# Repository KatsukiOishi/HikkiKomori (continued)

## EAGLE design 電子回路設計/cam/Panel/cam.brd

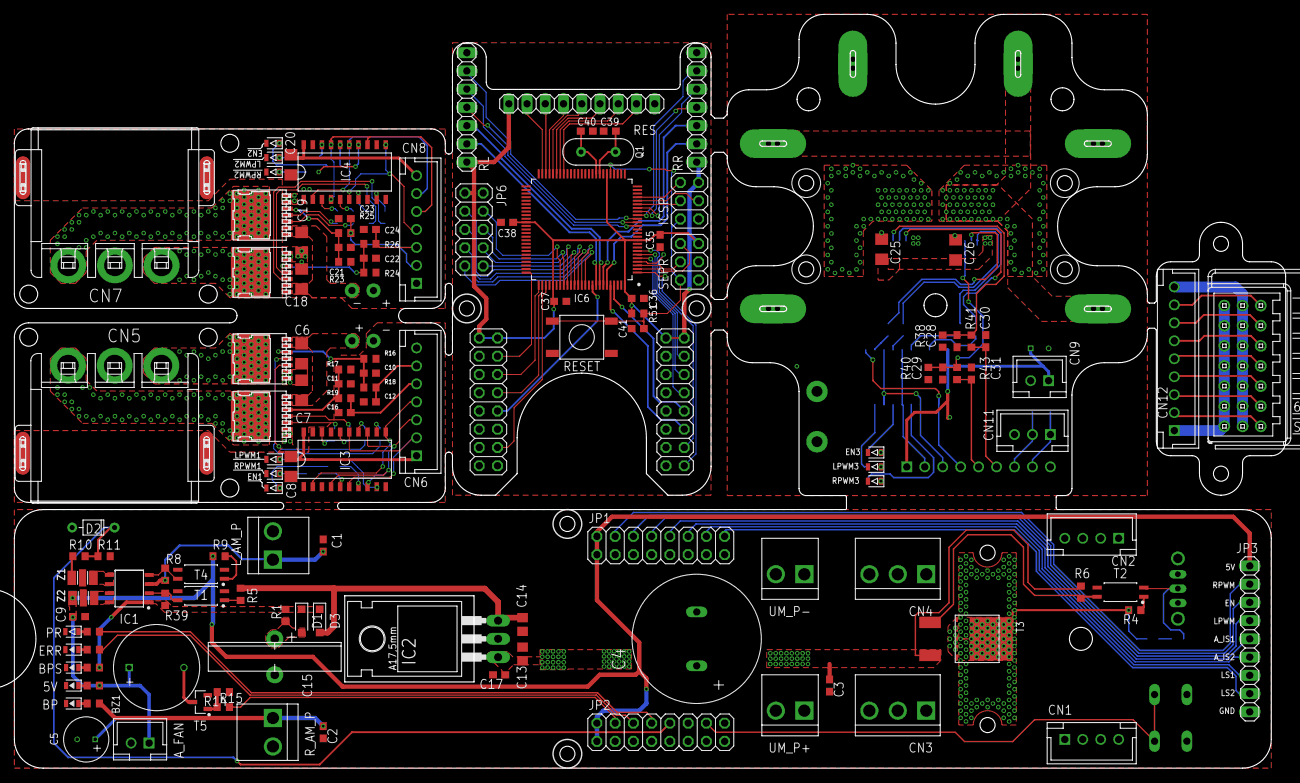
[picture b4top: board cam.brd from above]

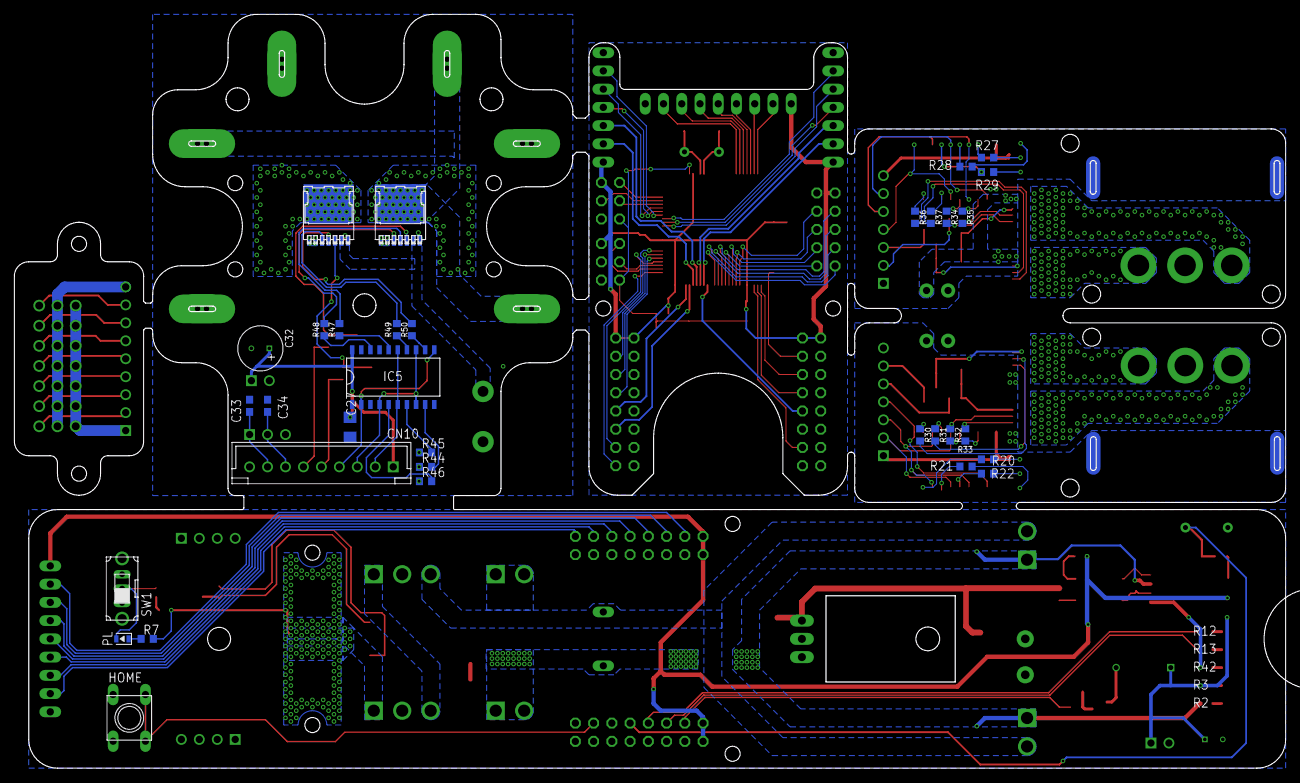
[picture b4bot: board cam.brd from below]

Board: 2 copper layers, 177.0 x 105.0 mm, 175 parts (33 on the bottom side), 171 nets.

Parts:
5V: OSBL1608C1A; LEDC1608X39N_B
A_FAN: B2B-XH-A
BP: OSBL1608C1A; LEDC1608X39N_B
BPS: OSBL1608C1A; LEDC1608X39N_B
BZ1: UGCM1205XP
C1, C2, C3, C9, C17, C35, C36, C37, C38: 0.1u; C0603
C4: 3300u; D18_L25_P7.5_D1
C5, C32: 100u; CPOL6.3-7_2.5
C6, C7, C8, C18, C19, C20, C25, C26, C27: 10u; C3216
C10, C11, C21, C22, C28, C29, C33, C34: 1n; C1608
C12, C16, C23, C24, C30, C31: 0.1u; C1608
C13, C14: 10u; C0805
C15: SE-5R5-D105VYV
C39, C40, C41: 22p; C0603
CN1, CN2: B4B-XH-A
CN3, CN4: B3P-VH
CN5, CN7: 798-HVH-280-3P-6.5DS
CN6, CN8: B7B-XH-A
CN9: B2B-XH-A
CN10, CN12: B9B-XH-A
CN11: B3B-XH-A
D1, D3: SS2040FL; SOD-123
D2: GDZJ5.1ADO-34; DIOAD590W50L290D210B
EN1, EN2, EN3: OSTG1608C1A; LEDC1608X39N_G
ERR: OSHR1608C1A; LEDC1608X39N_R
HOME: TS-0606-F-N-BLK; TS-0606-F-N
IC1: FDS4935A; SOIC127P600X250-8N
IC2: NJM7805FA-I; TO220
IC3, IC4, IC5: TC74HC244AF; SOP20
IC6: ATMEGA2560-16AU; QFP100
ICSP: 2X03
JP1, JP2, JP4, JP5: 2X08
JP3: 1X09
JP6: 2X05
LPWM1, LPWM2, LPWM3: OSTG1608C1A; LEDC1608X39N_G
L_AM_P: B2P-VH
OUT1: VIA_2.5X5.25_D0.75; VIA_2X5.25_D0.75
PL: OSBL1608C1A; LEDC1608X39N_B
PR: OSTG1608C1A; LEDC1608X39N_G
Q1: HUSG-16.000-20; XTALRR480W50L990T368H350B
R1, R15: 10; R0603
R2, R3, R7, R11, R12, R13, R14, R20, R21, R22, R27, R28, R29, R42, R44, R45, R46: 1k; R0603
R4: 480; R0603
R5, R9: 100; R0603
R6, R8, R39, R51: 10k; R0603
R10: 4.7k; R0603
R16, R17, R23, R24, R38, R40: 1.5k; R0603
R18, R19, R25, R26, R41, R43: 150; R0603
R30, R31, R32, R33, R34, R35, R36, R37, R47, R48, R49, R50: 10k; R1608
RES: 1X09
RESET: TS-06104
RL: 1X07
RPWM1, RPWM2, RPWM3: OSTG1608C1A; LEDC1608X39N_G
RR: 1X07
R_AM_P: B2P-VH
SEPR: 2X03
SW1: SS-12D01-VG4
T1, T2, T4: TLP291; SOIC127P700X210-4N
T3: TJ60S04M3L; DPACK
T5: IRLML6344TRPBF; SOT95P240X110-3N
U1, U2, U3, U4, U5, U6: BTN9990LV
U$1: R3006B
U$2, U$4, U$5, U$6, U$7, U$8, U$9, U$10, U$11, U$12, U$13: VIA_2.5X5.25_D0.75; VIA_2X5.25_D0.75
UM_P+: B2P-VH
UM_P-: B2P-VH
Z1, Z2: NFE31PT; NFE31

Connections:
5V: CN12.9, U$1.V1, U$1.V2, U$1.V3, U$1.V4, U$1.V5, U$1.V6, U$1.VB
5V1: IC1.7, IC1.8, Z2.1
+5V: A_FAN.1, BZ1.+, C5.+, C9.1, JP1.1, JP1.2, JP2.1, JP2.2, JP3.1, R3.2, R9.2, Z2.3
+5V1: C35.1, C36.1, C37.1, C38.1, IC6.10, IC6.31, IC6.61, IC6.80, IC6.100, ICSP.2, JP4.1, JP4.2, JP5.1, JP5.2, JP6.1, R51.2, RES.1, RL.1, RR.1, SEPR.2
+18V: CN3.1, R4.2, R7.2, T3.2
A_DIR: IC6.5, JP4.8
A_EN: IC6.6, JP4.6
A_IS1: JP1.10, JP3.5
A_IS2: JP1.12, JP3.6
A_IS3: IC6.97, JP4.10
A_IS4: IC6.96, JP4.12
A_PWM: IC6.7, JP4.4
BLINE2: CN3.3, CN4.1
BPS_LINE: D1.1, D3.1, IC1.1, R1.2, R39.2, R42.2
BPS_OR: C15.+, D1.2, R1.1
BUZ: JP2.4, R15.2
BUZ1: IC6.75, JP5.4
EN: JP1.6, JP3.3
EN1: CN6.3, IC3.4, IC3.8, IC3.13
EN2: CN8.5, IC4.4, IC4.13, IC4.17
EN3: CN10.3, IC5.4, IC5.8, IC5.13
ERR_LED: JP2.6, R13.2
ERR_LED1: IC6.76, JP5.6
GND: 5V.2, A_FAN.2, BP.2, BPS.2, C1.2, C2.2, C3.2, C4.-, C5.-, C9.2, C13.2, C14.2, C15.-, C17.2, CN4.3, D2.2, ERR.2, HOME.T3, HOME.T4, IC2.2, JP1.3, JP1.5, JP1.7, JP1.9, JP1.11, JP1.13, JP1.15, JP2.3, JP2.5, JP2.7, JP2.9, JP2.11, JP2.12, JP2.13, JP2.15, JP2.16, JP3.9, L_AM_P.2, PR.K, R11.1, R14.1, R_AM_P.2, SW1.NO, T1.2, T1.3, T2.3, T4.2, T4.3, T5.2, UM_P-.1, UM_P-.2, Z1.2, Z2.2
GND1: C6.2, C7.2, C8.2, C10.2, C11.2, C12.2, C16.2, C18.2, C19.2, C20.2, C21.2, C22.2, C23.2, C24.2, CN5.P$1, CN5.P$2, CN5.P$3, CN5.P$4, CN6.7, CN7.P$1, CN7.P$2, CN7.P$3, CN7.P$4, CN8.1, EN1.K, EN2.K, IC3.1, IC3.10, IC3.19, IC4.1, IC4.10, IC4.19, LPWM1.K, LPWM2.K, R16.1, R17.1, R23.1, R24.1, RPWM1.K, RPWM2.K, U1.GND1, U1.GND2, U2.GND1, U2.GND2, U3.GND1, U3.GND2, U4.GND1, U4.GND2
GND2: C25.2, C26.2, C27.2, C28.2, C29.2, C30.2, C31.2, C32.-, C33.2, C34.2, CN9.2, CN10.9, CN11.3, EN3.K, IC5.1, IC5.10, IC5.19, LPWM3.K, R38.1, R40.1, RPWM3.K, U5.GND1, U5.GND2, U6.GND1, U6.GND2
GND3: C35.2, C36.2, C37.2, C38.2, C39.1, C40.1, C41.2, IC6.11, IC6.32, IC6.62, IC6.81, IC6.99, ICSP.6, JP4.3, JP4.5, JP4.7, JP4.9, JP4.11, JP4.13, JP4.15, JP5.3, JP5.5, JP5.7, JP5.9, JP5.11, JP5.12, JP5.13, JP5.15, JP5.16, JP6.2, RES.9, RESET.B1, RESET.B2, RL.7, RR.7, SEPR.6
GND4: CN12.1, U$1.0B, U$1.01, U$1.02, U$1.03, U$1.04, U$1.05, U$1.06
HOME_SW: HOME.T1, HOME.T2, JP2.14
HOME_SW1: IC6.78, JP5.14
IS1: C12.1, CN6.6, R18.1
IS1_A: C10.1, R16.2, R18.2, U1.IS
IS1_A1: C21.1, R23.2, R25.2, U3.IS
IS1_A2: C28.1, R38.2, R41.2, U5.IS
IS2: C16.1, CN6.5, R19.1
IS2_1: C11.1, R17.2, R19.2, U2.IS
IS2_2: C22.1, R24.2, R26.2, U4.IS
IS2_3: C29.1, R40.2, R43.2, U6.IS
IS3: C30.1, CN10.6, R41.1
IS4: C31.1, CN10.5, R43.1
IS12: C23.1, CN8.2, R25.1
IS22: C24.1, CN8.3, R26.1
LPWM: JP1.8, JP3.4
LPWM1: CN6.4, IC3.2, IC3.11
LPWM2: CN8.4, IC4.6, IC4.11
LPWM3: CN10.4, IC5.2, IC5.11
LS1: JP1.14, JP3.7
LS2: JP1.16, JP3.8
LS3: C33.1, CN10.8, CN11.1
LS4: C34.1, CN10.7, CN11.2
LS5: IC6.4, JP4.14
LS6: IC6.1, JP4.16
MISO: IC6.22, ICSP.1
MOSI: IC6.21, ICSP.4
unnamed: PL.1, R7.1
unnamed: BP.1, R2.1
unnamed: 5V.1, R3.1
unnamed: IC1.5, IC1.6, Z1.1
unnamed: C14.1, D3.2, IC2.3, R5.1
unnamed: R4.1, T2.1
unnamed: PL.2, SW1.COM, T2.2
unnamed: R6.2, T2.4, T3.1
unnamed: IC1.4, R8.1, T4.4
unnamed: PR.A, R12.1
unnamed: R9.1, T4.1
unnamed: R10.2, Z1.3
unnamed: IC1.2, R39.1, T1.4
unnamed: ERR.1, R13.1
unnamed: BZ1.-, T5.3
unnamed: R14.2, R15.1, T5.1
unnamed: R5.2, T1.1
unnamed: IC3.18, R33.1
unnamed: IC3.16, R32.1
unnamed: IC3.14, R31.1
unnamed: IC3.12, R30.1
unnamed: LPWM1.A, R20.1
unnamed: EN1.A, R21.1
unnamed: R22.1, RPWM1.A
unnamed: IC3.9, R20.2
unnamed: IC3.7, R21.2
unnamed: IC3.5, R22.2
unnamed: IC4.9, R36.1
unnamed: IC4.7, R37.1
unnamed: IC4.5, R34.1
unnamed: IC4.3, R35.1
unnamed: R27.1, RPWM2.A
unnamed: EN2.A, R28.1
unnamed: LPWM2.A, R29.1
unnamed: IC4.18, R27.2
unnamed: IC4.16, R28.2
unnamed: IC4.14, R29.2
unnamed: R30.2, U1.INH
unnamed: R31.2, U1.IN
unnamed: R32.2, U2.INH
unnamed: R33.2, U2.IN
unnamed: R34.2, U3.IN
unnamed: R35.2, U3.INH
unnamed: R36.2, U4.IN
unnamed: R37.2, U4.INH
unnamed: IC5.18, R48.1
unnamed: BPS.1, R42.1
unnamed: IC5.16, R47.1
unnamed: LPWM3.A, R44.1
unnamed: EN3.A, R45.1
unnamed: R46.1, RPWM3.A
unnamed: IC5.9, R44.2
unnamed: IC5.7, R45.2
unnamed: IC5.5, R46.2
unnamed: IC5.14, R49.1
unnamed: IC5.12, R50.1
unnamed: R47.2, U5.INH
unnamed: R48.2, U5.IN
unnamed: R49.2, U6.IN
unnamed: R50.2, U6.INH
unnamed: C40.2, IC6.34, Q1.1
unnamed: C39.2, IC6.33, Q1.2
unnamed: IC6.43, RES.8
unnamed: IC6.44, RES.7
unnamed: IC6.45, RES.6
unnamed: IC6.46, RES.5
unnamed: IC6.47, RES.4
unnamed: IC6.48, RES.3
unnamed: IC6.49, RES.2
unnamed: IC6.89, JP6.9
unnamed: IC6.88, JP6.7
unnamed: IC6.87, JP6.5
unnamed: IC6.86, JP6.3
unnamed: IC6.85, JP6.10
unnamed: IC6.84, JP6.8
unnamed: IC6.83, JP6.6
unnamed: IC6.82, JP6.4
unnamed: CN12.8, U$1.1
unnamed: CN12.7, U$1.2
unnamed: CN12.6, U$1.3
unnamed: CN12.5, U$1.4
unnamed: CN12.4, U$1.5
unnamed: CN12.3, U$1.6
unnamed: CN12.2, U$1.B
OUT1: CN5.1, U1.OUT
OUT2: CN5.3, U2.OUT
OUT3: CN7.1, U3.OUT
OUT4: CN7.3, U4.OUT
OUT5: OUT1.P$1, U5.OUT, U$2.P$1, U$4.P$1, U$5.P$1, U$6.P$1, U$7.P$1
OUT6: U6.OUT, U$8.P$1, U$9.P$1, U$10.P$1, U$11.P$1, U$12.P$1, U$13.P$1
PR_LED: JP2.8, R12.2
PR_LED1: IC6.77, JP5.8
PW_AD: D2.1, JP2.10, R10.1, R11.2
PW_AD1: IC6.91, JP5.10
RESET: C41.1, IC6.30, ICSP.5, R51.1, RESET.A1, RESET.A2, SEPR.5
RL_DIR: IC6.16, RL.6
RL_EN: IC6.14, RL.5
RL_IS1: IC6.92, RL.2
RL_IS2: IC6.93, RL.3
RL_PWM: IC6.15, RL.4
RPWM: JP1.4, JP3.2
RPWM1: CN6.2, IC3.6, IC3.15
RPWM2: CN8.6, IC4.2, IC4.15
RPWM3: CN10.2, IC5.6, IC5.15
RR_DIR: IC6.17, RR.6
RR_EN: IC6.19, RR.5
RR_IS1: IC6.95, RR.2
RR_IS2: IC6.94, RR.3
RR_PWM: IC6.18, RR.4
RX1: IC6.2, SEPR.1
SCK: IC6.20, ICSP.3
TX1: IC6.3, SEPR.3
VCC: C8.1, C20.1, CN6.1, CN8.7, IC3.20, IC4.20
VCC1: C27.1, C32.+, CN9.1, CN10.1, IC5.20
VDD: C1.1, C2.1, C3.1, C4.+, C13.1, C17.1, IC1.3, IC2.1, L_AM_P.1, R2.2, R6.1, R8.2, R_AM_P.1, T3.3, UM_P+.1, UM_P+.2
VDD1: C6.1, C7.1, C18.1, C19.1, U1.VS1, U1.VS2, U2.VS1, U2.VS2, U3.VS1, U3.VS2, U4.VS1, U4.VS2
VDD2: C25.1, C26.1, U5.VS1, U5.VS2, U6.VS1, U6.VS2

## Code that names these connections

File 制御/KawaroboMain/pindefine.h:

#ifndef _PINDEFINE_H_
#define _PINDEFINE_H_

#define A_EN    2
#define A_RPWM   3
#define A_LPWM   5
#define A_IS1   A0
#define A_IS2   A1
#define LS1     70
#define LS2     4

#define RL_EN   73
#define RL_RPWM  7
#define RL_LPWM  6
#define RL_IS1  A5
#define RL_IS2  A4
#define RR_EN   53
#define RR_RPWM  8
#define RR_LPWM  9
#define RR_IS1  A2
#define RR_IS2  A3

#define BUZ     25
#define PR_LED  23
#define ERR_LED 24
#define PW_AD   A6
#define HOME_SW 22

#define DLS LS1
#define ULS LS2
#endif

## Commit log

2022-05-22 gitignore追加
2022-05-22 2017年用参考データ追加
2022-05-23 左半身側ヘッケンリンク作成
2022-05-23 右半身側単体足作成
2022-05-23 不要データ削除
2022-05-24 左半身完成
2022-05-25 左半身詳細設計
2022-05-31 中央ユニット作成
2022-06-01 アームリンク各種作図完了
2022-06-01 アームリンク作成
2022-06-01 腕機構仮決定
2022-06-01 全体像策定完了
2022-06-04 ワイヤ長さ決定 ワイヤブロック作成
2022-06-04 これからどうかっしゃにするよー（絶望）
2022-06-04 定荷重バネ追加・展開バネ決定
2022-06-10 バネ展開機構構想設計済
2022-06-12 足駆動回路仮決定完了
2022-06-12 足駆動回路ヒートシンク仮設計
2022-06-13 ・足駆動回路設計完 ・足駆動回路ミラーバージョン作成
2022-06-14 腕機構リミットスイッチ配置完了 close #5
2022-06-14 腕駆動回路設計開始
2022-06-16 腕駆動回路設計完
2022-11-24 point
2023-07-12 point : circuit desgine comp
2023-07-12 add : AMD add res
2023-07-12 add : AMD cam
2023-07-12 fix : RMD cap
2023-07-12 fix : RMD res / add : RMD cam
2023-07-12 add : RMDRES cap
2023-07-12 add : cams
2023-07-12 add : boards asm
2023-07-12 fix : CB fix error
2023-07-12 add : CBv4 3dCAD
2023-07-12 upd : circuit board unit update
2023-07-12 fix : CB cam
2023-07-12 fix : cam data
2023-07-12 fix : link sus parts screw shape
2023-07-12 add : RR001 drawing
2023-07-12 fix : RR pinion gear
2023-07-12 point : RR BOM ready comp
2023-07-12 add : R-SA001.1 drawing
2023-07-12 point : RR-HL001 BOM ready comp
2023-07-12 point : RR-HL-RAS001 BOM ready comp
2023-07-12 point : RR-HL-RAS002 BOM ready comp
2023-07-12 point : Export RR BOMs
2023-07-13 fix : CU fix
2023-07-13 add : RL001 profile add
2023-07-13 fix : RL001 pinion gear
2023-07-13 fix : RR001 parts PartNo fix
2023-07-13 add : RL001 subasm and parts profile fix
2023-07-13 add : RL001 drawing
2023-07-13 add : RL-HL002 drawing
2023-07-13 fix : RR-HR-RAS001 bom fix
2023-07-13 add : RL-HL-RAS001 bom
2023-07-13 point : RL001 BOM comp (close #16)
2023-07-13 add : CU001 profiles add
2023-07-13 add : CU001 BOM
2023-07-13 add : CU-SAS003 drawing
2023-07-13 point : CU-SAS003 asem fix
2023-07-13 add : CU-SAS003 BOM
2023-07-13 fix : CU-SAS001 parts fix
2023-07-13 add : CU-SAS001 drawing
2023-07-13 add : CU-SAS001 BOM (close #20)
2023-07-13 point : CGA75 profile add
2023-07-13 point : CU-SAS002 parts profile fix (other arm parts)
2023-07-13 point : CU-SAS002 arm parts profile fix
2023-07-13 add : CU-SAS002 drawing
2023-07-13 add : CU-SAS002 BOM (close #22)
2023-07-13 add : CU-SAS002 BOM
2023-07-13 fix : CU-SAS002 BOM
2023-07-13 add : CU-AAS001 drawing
2023-07-13 add : CU-AAS001 bom
2023-07-13 point : CU-AAS002 profile add
2023-07-13 add : CU-AAS002 bom
2023-07-13 add : CU-AAS003L drawingm
2023-07-13 add : CU-AAS003L bom
2023-07-13 add : CU-AAS003R bom (close #26)
2023-07-13 point : CGA75-RS380-4 parts profile fix
2023-07-13 add : CGA75-RS380-4 drawing
2023-07-13 fix : CGA75 parts profiles
2023-07-13 add : CGA75 drawing
2023-07-13 add : CGA75 bom
2023-07-15 fix : CU-P002 screw hole
2023-07-15 add : circuit spacer (close #23)
2023-07-15 fix : AAS002-P002/3 shape fix
2023-07-15 add : plunger add
2023-07-16 add : counter arm
2023-07-16 point : counter arm desgine comp.(close #2)
2023-07-16 point : desgine comp.
2023-07-16 point : desgine comp (close #10)
2023-07-16 add : CGA75-RS380-4 BOM
2023-07-16 point : bom asem comp.
2023-07-18 add : BOM add manuBOM
2023-07-18 add : CGA75-P001 CAM
2023-07-18 add : CAM files
2023-07-27 point : CAM_T3_2 cam comp
2023-07-28 point : CAM_T2_1 cam comp
2023-07-28 point : CAM_T2_2 cam comp
2023-07-29 point : CAM_T12_1 cam comp
2023-07-29 point : CAM_T2_3 cam comp
2023-07-30 add : CAM_t3_3
2023-08-18 point : make comp
2023-08-18 add : Arduino work space
2023-08-18 add : motordrive.hpp
2023-08-19 point : add read res
2023-08-26 point : 本番前
2024-06-11 fix : file broken
2024-09-02 装甲板追加、リンクサス改良、カバー材質変更
2025-05-29 add : 第30回用設計基本書
2025-05-29 add : 長ねじ挿入
2025-05-29 point : CAD修正終了
